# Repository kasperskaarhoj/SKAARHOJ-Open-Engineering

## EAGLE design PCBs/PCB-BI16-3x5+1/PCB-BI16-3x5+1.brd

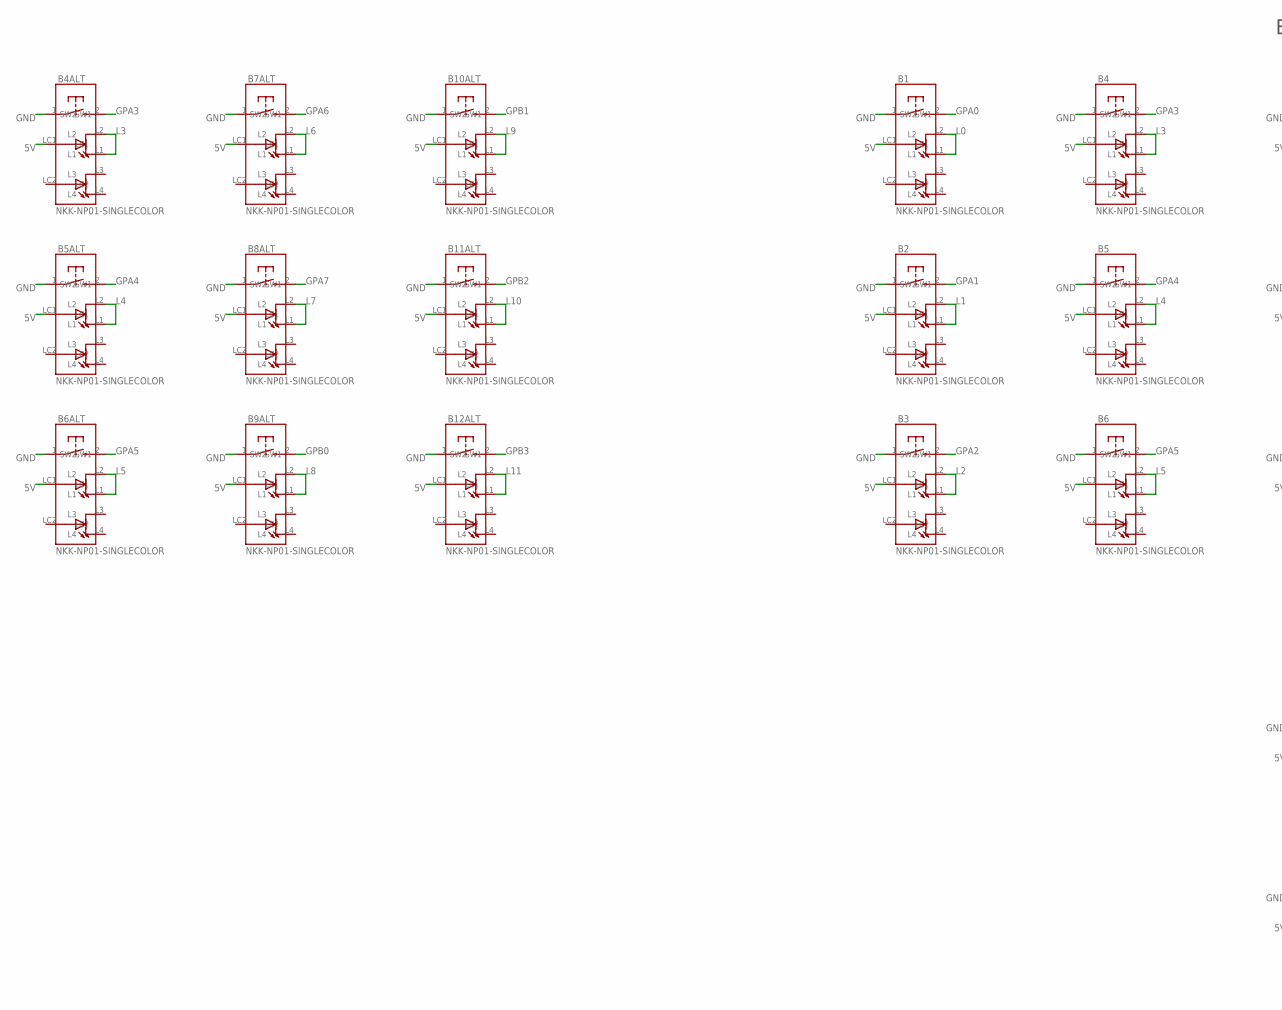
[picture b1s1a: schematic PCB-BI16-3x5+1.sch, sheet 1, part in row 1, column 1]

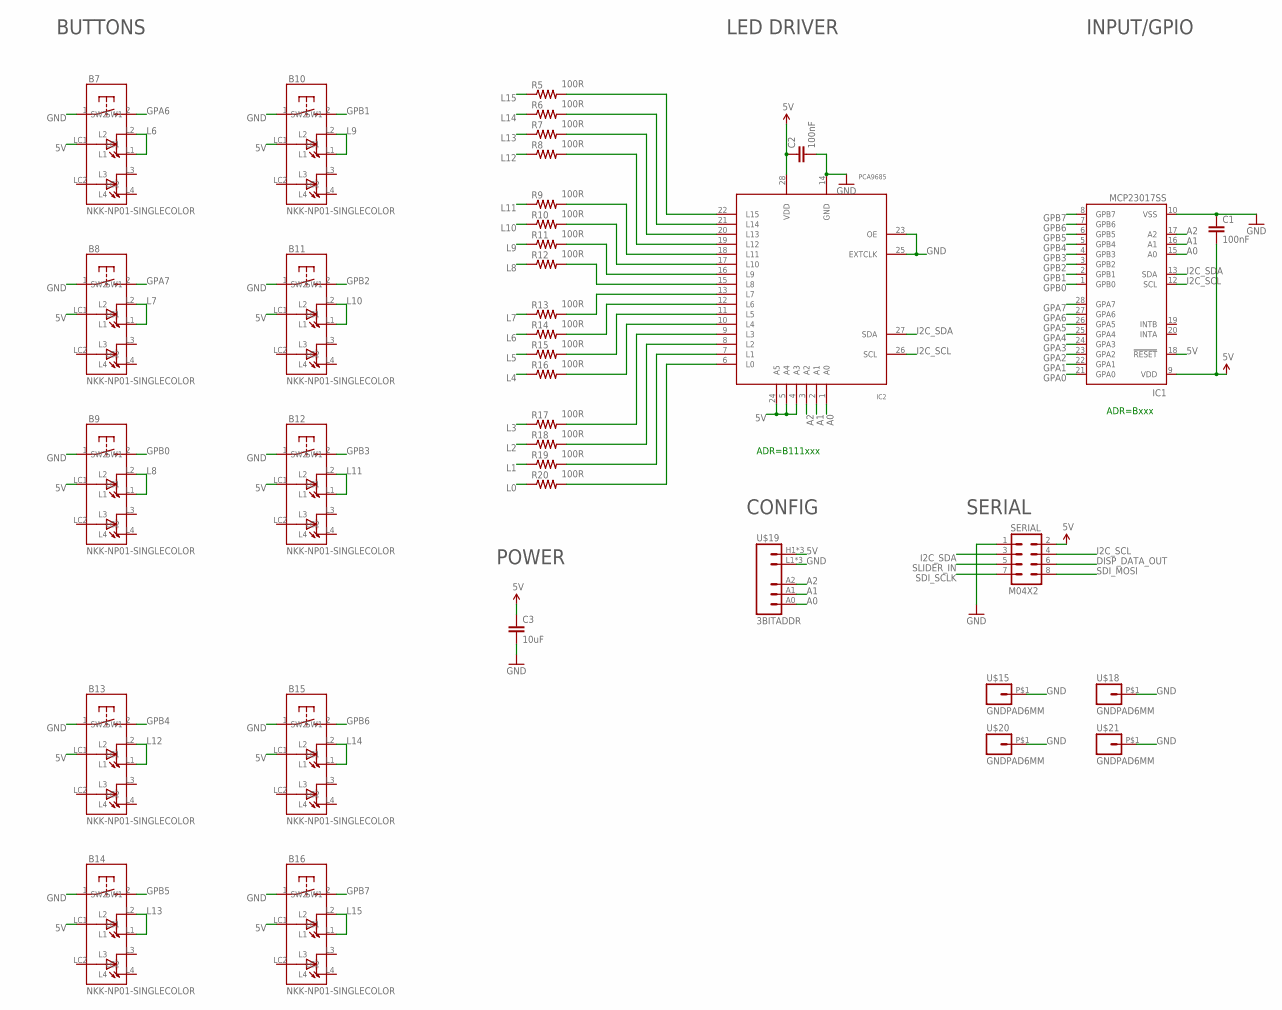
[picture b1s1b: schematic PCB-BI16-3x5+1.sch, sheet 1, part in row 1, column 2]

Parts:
B1, B2, B3, B4, B4ALT, B5, B5ALT, B6, B6ALT, B7, B7ALT, B8, B8ALT, B9, B9ALT, B10, B10ALT, B11, B11ALT, B12, B12ALT, B13, B14, B15, B16: NKK-NP01-SINGLECOLOR; NKK-NP01
C1, C2: 100nF; 0603-CAP
C3: 10uF; 0805
IC1: MCP23017SS; SSOP28; MPN MCP23017-E/SS
IC2: PCA9685; TSSOP28
R5, R6, R7, R8, R9, R10, R11, R12, R13, R14, R15, R16, R17, R18, R19, R20: 100R; 0603-RES
SERIAL: M04X2; 2X4
U$15, U$18, U$20, U$21: GNDPAD6MM; 3.2MMPAD6MM
U$19: 3BITADDR

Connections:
5V: B1.LC1, B2.LC1, B3.LC1, B4.LC1, B4ALT.LC1, B5.LC1, B5ALT.LC1, B6.LC1, B6ALT.LC1, B7.LC1, B7ALT.LC1, B8.LC1, B8ALT.LC1, B9.LC1, B9ALT.LC1, B10.LC1, B10ALT.LC1, B11.LC1, B11ALT.LC1, B12.LC1, B12ALT.LC1, B13.LC1, B14.LC1, B15.LC1, B16.LC1, C1.2, C2.1, C3.1, IC1.9 (VDD), IC1.18 (!RESET), IC2.4 (A3), IC2.5 (A4), IC2.24 (A5), IC2.28 (VDD), SERIAL.2, U$19.H1 (VCC), U$19.H2 (VCC), U$19.H3 (VCC)
A0: IC1.15 (A0), IC2.1 (A0), U$19.A0
A1: IC1.16 (A1), IC2.2 (A1), U$19.A1
A2: IC1.17 (A2), IC2.3 (A2), U$19.A2
DISP_DATA_OUT: SERIAL.6
GND: B1.1 (SW1), B2.1 (SW1), B3.1 (SW1), B4.1 (SW1), B4ALT.1 (SW1), B5.1 (SW1), B5ALT.1 (SW1), B6.1 (SW1), B6ALT.1 (SW1), B7.1 (SW1), B7ALT.1 (SW1), B8.1 (SW1), B8ALT.1 (SW1), B9.1 (SW1), B9ALT.1 (SW1), B10.1 (SW1), B10ALT.1 (SW1), B11.1 (SW1), B11ALT.1 (SW1), B12.1 (SW1), B12ALT.1 (SW1), B13.1 (SW1), B14.1 (SW1), B15.1 (SW1), B16.1 (SW1), C1.1, C2.2, C3.2, IC1.10 (VSS), IC2.14 (GND), IC2.23 (OE), IC2.25 (EXTCLK), SERIAL.1, U$15.P$1, U$18.P$1, U$19.L1 (GND), U$19.L2 (GND), U$19.L3 (GND), U$20.P$1, U$21.P$1
GPA0: B1.2 (SW2), IC1.21 (GPA0)
GPA1: B2.2 (SW2), IC1.22 (GPA1)
GPA2: B3.2 (SW2), IC1.23 (GPA2)
GPA3: B4.2 (SW2), B4ALT.2 (SW2), IC1.24 (GPA3)
GPA4: B5.2 (SW2), B5ALT.2 (SW2), IC1.25 (GPA4)
GPA5: B6.2 (SW2), B6ALT.2 (SW2), IC1.26 (GPA5)
GPA6: B7.2 (SW2), B7ALT.2 (SW2), IC1.27 (GPA6)
GPA7: B8.2 (SW2), B8ALT.2 (SW2), IC1.28 (GPA7)
GPB0: B9.2 (SW2), B9ALT.2 (SW2), IC1.1 (GPB0)
GPB1: B10.2 (SW2), B10ALT.2 (SW2), IC1.2 (GPB1)
GPB2: B11.2 (SW2), B11ALT.2 (SW2), IC1.3 (GPB2)
GPB3: B12.2 (SW2), B12ALT.2 (SW2), IC1.4 (GPB3)
GPB4: B13.2 (SW2), IC1.5 (GPB4)
GPB5: B14.2 (SW2), IC1.6 (GPB5)
GPB6: B15.2 (SW2), IC1.7 (GPB6)
GPB7: B16.2 (SW2), IC1.8 (GPB7)
I2C_SCL: IC1.12 (SCL), IC2.26 (SCL), SERIAL.4
I2C_SDA: IC1.13 (SDA), IC2.27 (SDA), SERIAL.3
L0: B1.L1, B1.L2, R20.1
L1: B2.L1, B2.L2, R19.1
L2: B3.L1, B3.L2, R18.1
L3: B4.L1, B4.L2, B4ALT.L1, B4ALT.L2, R17.1
L4: B5.L1, B5.L2, B5ALT.L1, B5ALT.L2, R16.1
L5: B6.L1, B6.L2, B6ALT.L1, B6ALT.L2, R15.1
L6: B7.L1, B7.L2, B7ALT.L1, B7ALT.L2, R14.1
L7: B8.L1, B8.L2, B8ALT.L1, B8ALT.L2, R13.1
L8: B9.L1, B9.L2, B9ALT.L1, B9ALT.L2, R12.1
L9: B10.L1, B10.L2, B10ALT.L1, B10ALT.L2, R11.1
L10: B11.L1, B11.L2, B11ALT.L1, B11ALT.L2, R10.1
L11: B12.L1, B12.L2, B12ALT.L1, B12ALT.L2, R9.1
L12: B13.L1, B13.L2, R8.1
L13: B14.L1, B14.L2, R7.1
L14: B15.L1, B15.L2, R6.1
L15: B16.L1, B16.L2, R5.1
unnamed: IC2.13 (L7), R13.2
unnamed: IC2.12 (L6), R14.2
unnamed: IC2.11 (L5), R15.2
unnamed: IC2.10 (L4), R16.2
unnamed: IC2.9 (L3), R17.2
unnamed: IC2.8 (L2), R18.2
unnamed: IC2.7 (L1), R19.2
unnamed: IC2.6 (L0), R20.2
unnamed: IC2.15 (L8), R12.2
unnamed: IC2.16 (L9), R11.2
unnamed: IC2.17 (L10), R10.2
unnamed: IC2.18 (L11), R9.2
unnamed: IC2.19 (L12), R8.2
unnamed: IC2.20 (L13), R7.2
unnamed: IC2.21 (L14), R6.2
unnamed: IC2.22 (L15), R5.2
SDI_MOSI: SERIAL.8
SDI_SCLK: SERIAL.7
SLIDER_IN: SERIAL.5

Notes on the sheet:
ADR=B111xxx
ADR=Bxxx
BUTTONS
LED DRIVER
INPUT/GPIO
POWER
SERIAL
CONFIG

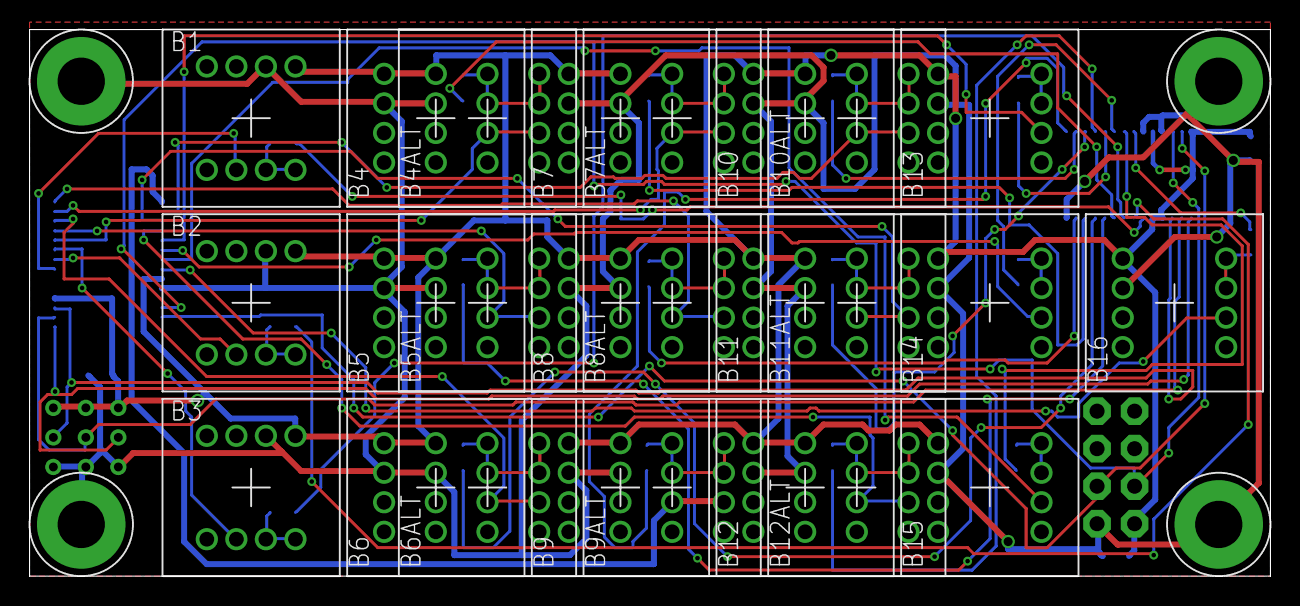
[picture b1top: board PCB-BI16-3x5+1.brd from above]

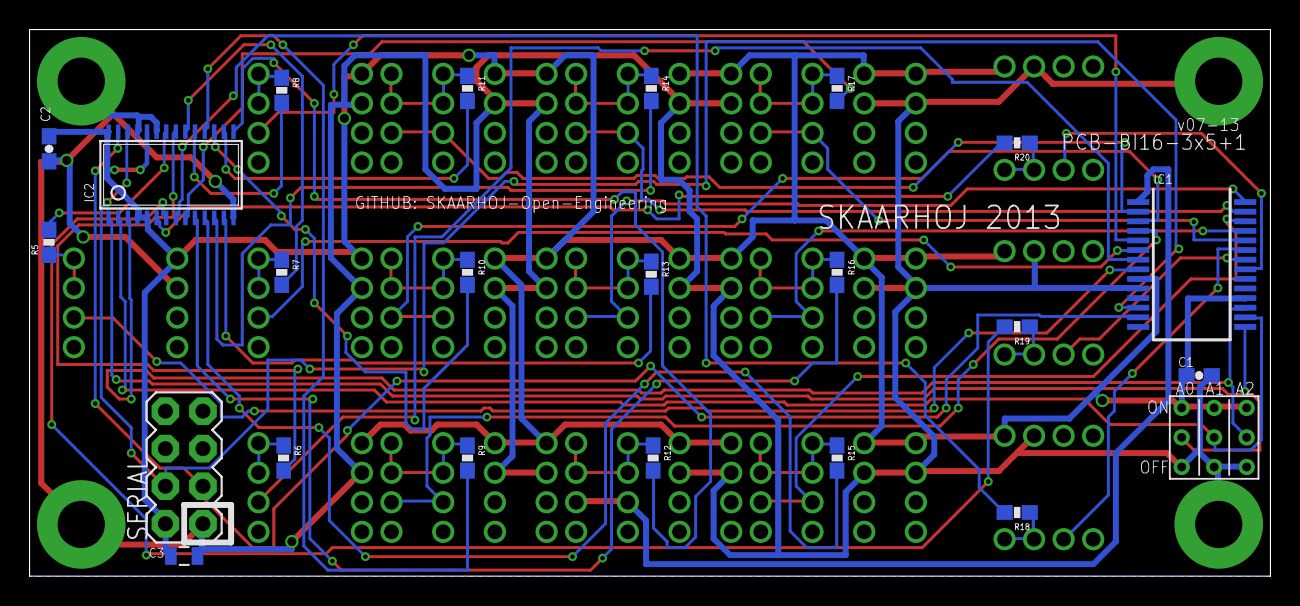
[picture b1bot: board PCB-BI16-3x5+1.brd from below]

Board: 2 copper layers, 84.0 x 37.0 mm, 52 parts (23 on the bottom side), 55 nets.

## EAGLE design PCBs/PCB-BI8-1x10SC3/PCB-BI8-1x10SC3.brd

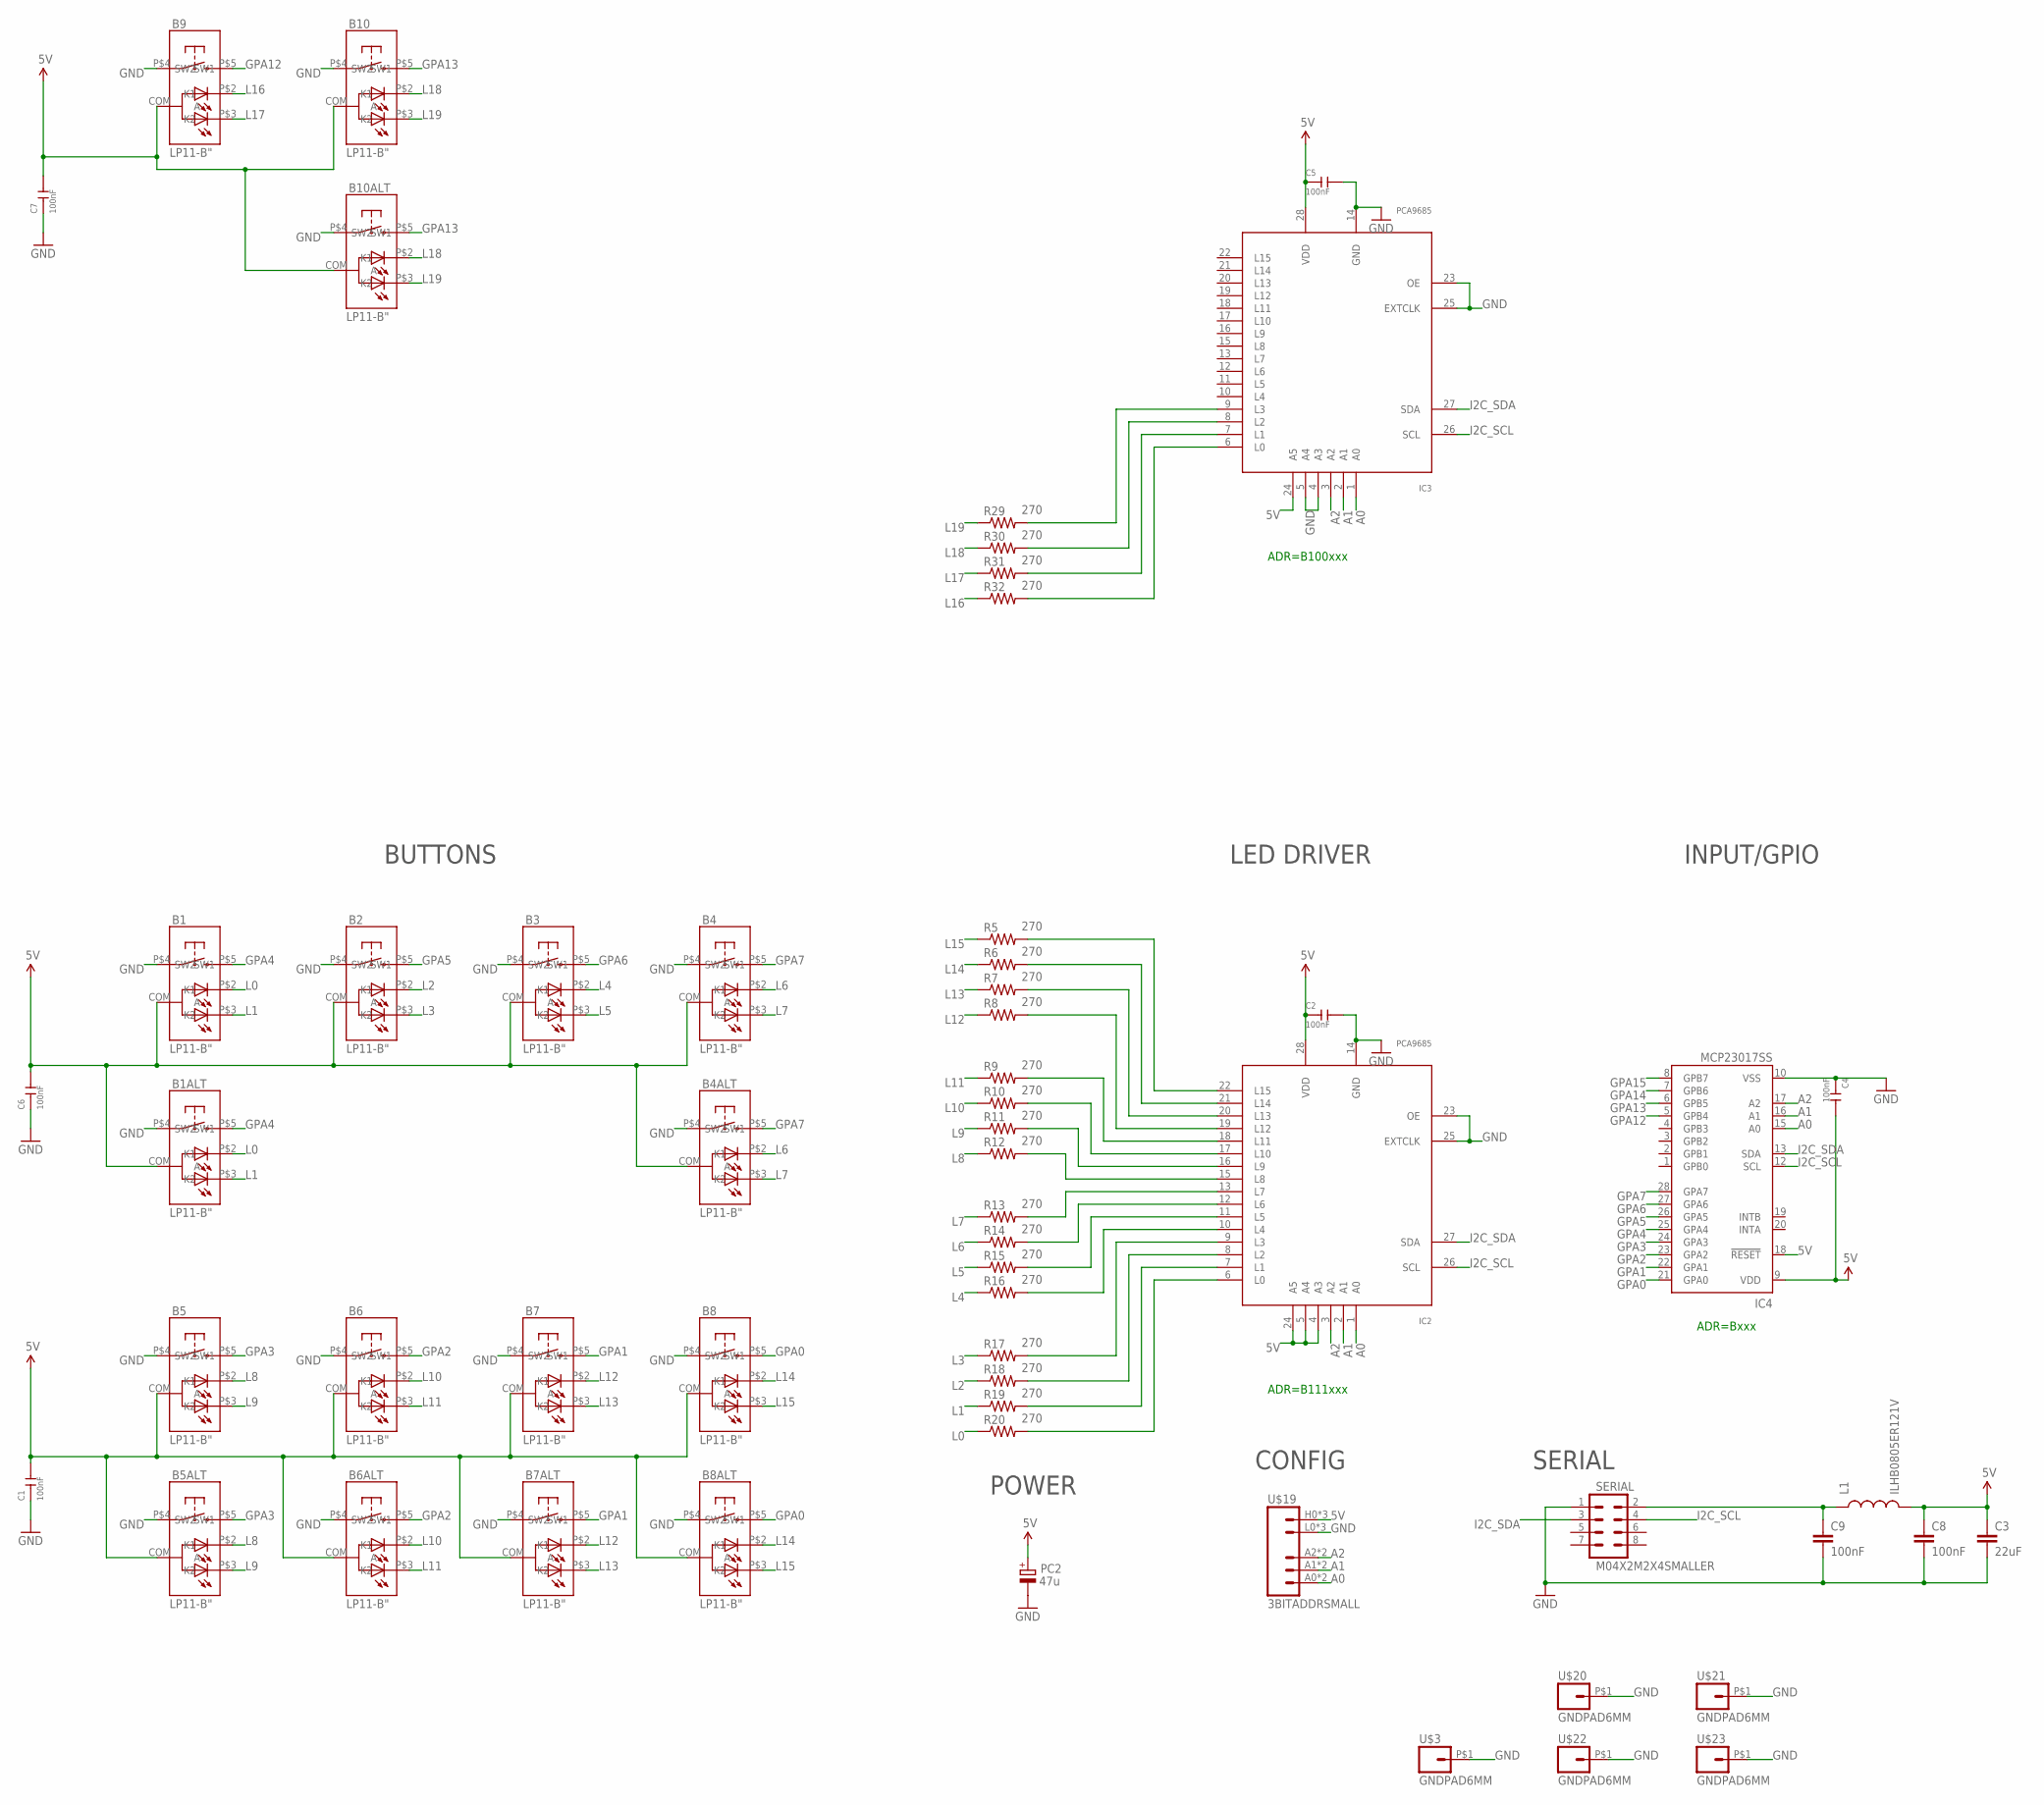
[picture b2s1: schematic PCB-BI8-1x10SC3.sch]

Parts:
B1, B1ALT, B2, B3, B4, B4ALT, B5, B5ALT, B6, B6ALT, B7, B7ALT, B8, B8ALT, B9, B10, B10ALT: LP11-B"; LP11
C1, C2, C4, C5, C6, C7: 100nF; C0603
C3: 22uF; 0805
C8, C9: 100nF; 0603-CAP
IC2, IC3: PCA9685; TSSOP28
IC4: MCP23017SS; SSOP28; MPN MCP23017-E/SS
L1: ILHB0805ER121V; 0805
PC2: 47u; PANASONIC_D
R5, R6, R7, R8, R9, R10, R11, R12, R13, R14, R15, R16, R17, R18, R19, R20, R29, R30, R31, R32: 270; 0603-RES
SERIAL: M04X2M2X4SMALLER; M2X4SMALLER
U$3, U$20, U$21, U$22, U$23: GNDPAD6MM; 3.2MMPAD6MM
U$19: 3BITADDRSMALL; 3BITADDR_SMALL

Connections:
5V: B1.COM (A), B1ALT.COM (A), B2.COM (A), B3.COM (A), B4.COM (A), B4ALT.COM (A), B5.COM (A), B5ALT.COM (A), B6.COM (A), B6ALT.COM (A), B7.COM (A), B7ALT.COM (A), B8.COM (A), B8ALT.COM (A), B9.COM (A), B10.COM (A), B10ALT.COM (A), C1.2, C2.1, C3.1, C4.2, C5.1, C6.2, C7.2, C8.1, IC2.4 (A3), IC2.5 (A4), IC2.24 (A5), IC2.28 (VDD), IC3.24 (A5), IC3.28 (VDD), IC4.9 (VDD), IC4.18 (!RESET), L1.2, PC2.+, U$19.H0 (VCC), U$19.H1 (VCC), U$19.H2 (VCC)
A0: IC2.1 (A0), IC3.1 (A0), IC4.15 (A0), U$19.A0, U$19.AS0 (A0)
A1: IC2.2 (A1), IC3.2 (A1), IC4.16 (A1), U$19.A1, U$19.AS1 (A1)
A2: IC2.3 (A2), IC3.3 (A2), IC4.17 (A2), U$19.A2, U$19.AS2 (A2)
GND: B1.P$4 (SW1), B1ALT.P$4 (SW1), B2.P$4 (SW1), B3.P$4 (SW1), B4.P$4 (SW1), B4ALT.P$4 (SW1), B5.P$4 (SW1), B5ALT.P$4 (SW1), B6.P$4 (SW1), B6ALT.P$4 (SW1), B7.P$4 (SW1), B7ALT.P$4 (SW1), B8.P$4 (SW1), B8ALT.P$4 (SW1), B9.P$4 (SW1), B10.P$4 (SW1), B10ALT.P$4 (SW1), C1.1, C2.2, C3.2, C4.1, C5.2, C6.1, C7.1, C8.2, C9.2, IC2.14 (GND), IC2.23 (OE), IC2.25 (EXTCLK), IC3.4 (A3), IC3.5 (A4), IC3.14 (GND), IC3.23 (OE), IC3.25 (EXTCLK), IC4.10 (VSS), PC2.-, SERIAL.1, U$3.P$1, U$19.L0 (GND), U$19.L1 (GND), U$19.L2 (GND), U$20.P$1, U$21.P$1, U$22.P$1, U$23.P$1
GPA0: B8.P$5 (SW2), B8ALT.P$5 (SW2), IC4.21 (GPA0)
GPA1: B7.P$5 (SW2), B7ALT.P$5 (SW2), IC4.22 (GPA1)
GPA2: B6.P$5 (SW2), B6ALT.P$5 (SW2), IC4.23 (GPA2)
GPA3: B5.P$5 (SW2), B5ALT.P$5 (SW2), IC4.24 (GPA3)
GPA4: B1.P$5 (SW2), B1ALT.P$5 (SW2), IC4.25 (GPA4)
GPA5: B2.P$5 (SW2), IC4.26 (GPA5)
GPA6: B3.P$5 (SW2), IC4.27 (GPA6)
GPA7: B4.P$5 (SW2), B4ALT.P$5 (SW2), IC4.28 (GPA7)
GPA12: B9.P$5 (SW2), IC4.5 (GPB4)
GPA13: B10.P$5 (SW2), B10ALT.P$5 (SW2), IC4.6 (GPB5)
GPA14: IC4.7 (GPB6)
GPA15: IC4.8 (GPB7)
I2C_SCL: IC2.26 (SCL), IC3.26 (SCL), IC4.12 (SCL), SERIAL.4
I2C_SDA: IC2.27 (SDA), IC3.27 (SDA), IC4.13 (SDA), SERIAL.3
L0: B1.P$2 (K1), B1ALT.P$2 (K1), R20.1
L1: B1.P$3 (K2), B1ALT.P$3 (K2), R19.1
L2: B2.P$2 (K1), R18.1
L3: B2.P$3 (K2), R17.1
L4: B3.P$2 (K1), R16.1
L5: B3.P$3 (K2), R15.1
L6: B4.P$2 (K1), B4ALT.P$2 (K1), R14.1
L7: B4.P$3 (K2), B4ALT.P$3 (K2), R13.1
L8: B5.P$2 (K1), B5ALT.P$2 (K1), R12.1
L9: B5.P$3 (K2), B5ALT.P$3 (K2), R11.1
L10: B6.P$2 (K1), B6ALT.P$2 (K1), R10.1
L11: B6.P$3 (K2), B6ALT.P$3 (K2), R9.1
L12: B7.P$2 (K1), B7ALT.P$2 (K1), R8.1
L13: B7.P$3 (K2), B7ALT.P$3 (K2), R7.1
L14: B8.P$2 (K1), B8ALT.P$2 (K1), R6.1
L15: B8.P$3 (K2), B8ALT.P$3 (K2), R5.1
L16: B9.P$2 (K1), R32.1
L17: B9.P$3 (K2), R31.1
L18: B10.P$2 (K1), B10ALT.P$2 (K1), R30.1
L19: B10.P$3 (K2), B10ALT.P$3 (K2), R29.1
unnamed: C9.1, L1.1, SERIAL.2
unnamed: IC2.13 (L7), R13.2
unnamed: IC2.12 (L6), R14.2
unnamed: IC2.11 (L5), R15.2
unnamed: IC3.9 (L3), R29.2
unnamed: IC2.10 (L4), R16.2
unnamed: IC2.9 (L3), R17.2
unnamed: IC2.8 (L2), R18.2
unnamed: IC2.7 (L1), R19.2
unnamed: IC3.8 (L2), R30.2
unnamed: IC3.7 (L1), R31.2
unnamed: IC3.6 (L0), R32.2
unnamed: IC2.6 (L0), R20.2
unnamed: IC2.15 (L8), R12.2
unnamed: IC2.16 (L9), R11.2
unnamed: IC2.17 (L10), R10.2
unnamed: IC2.18 (L11), R9.2
unnamed: IC2.19 (L12), R8.2
unnamed: IC2.20 (L13), R7.2
unnamed: IC2.21 (L14), R6.2
unnamed: IC2.22 (L15), R5.2

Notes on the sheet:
ADR=B111xxx
BUTTONS
LED DRIVER
INPUT/GPIO
POWER
SERIAL
CONFIG
ADR=B100xxx
ADR=Bxxx

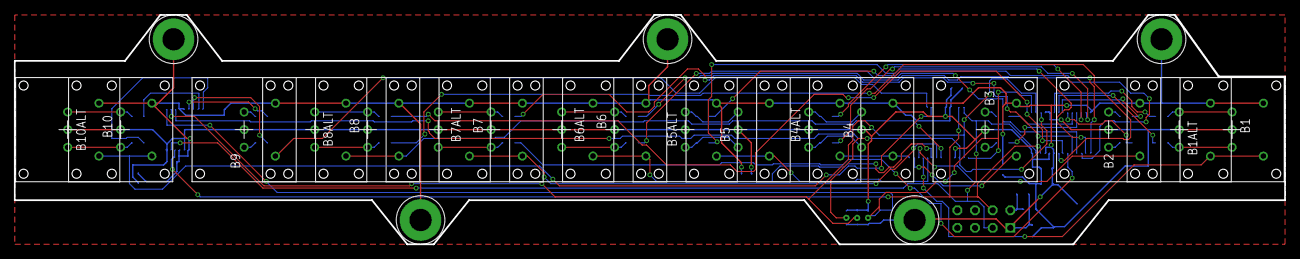
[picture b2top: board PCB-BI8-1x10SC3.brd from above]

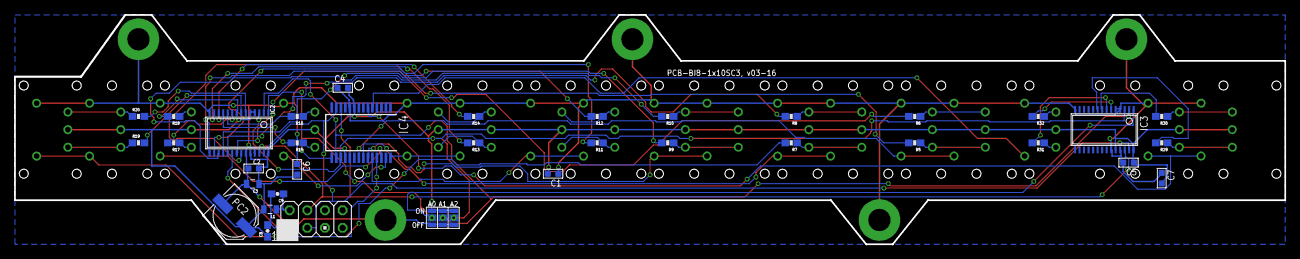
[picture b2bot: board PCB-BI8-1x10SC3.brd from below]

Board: 2 copper layers, 182.9 x 33.0 mm, 58 parts (36 on the bottom side), 58 nets.

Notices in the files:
parts and their libraries:
SparkFun: Licensing: CC v3.0 Share-Alike You are welcome to use this library for commercial purposes.
